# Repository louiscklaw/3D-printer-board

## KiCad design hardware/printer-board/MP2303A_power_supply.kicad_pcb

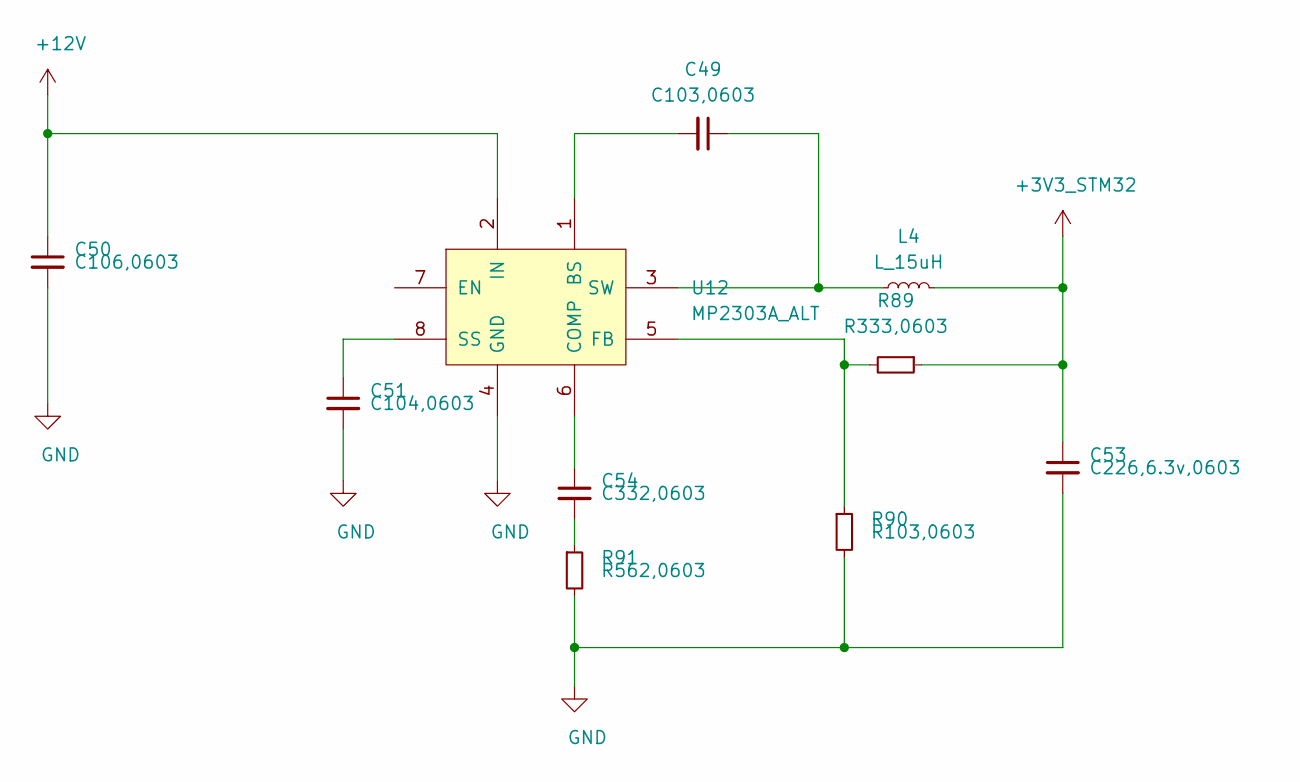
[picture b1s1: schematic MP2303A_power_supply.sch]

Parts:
C49: C103,0603; C_0603_1608Metric_Pad1.05x0.95mm_HandSolder
C50: C106,0603; C_0603_1608Metric_Pad1.05x0.95mm_HandSolder
C51: C104,0603; C_0603_1608Metric_Pad1.05x0.95mm_HandSolder
C53: C226,6.3v,0603; C_0603_1608Metric_Pad1.05x0.95mm_HandSolder
C54: C332,0603; C_0603_1608Metric_Pad1.05x0.95mm_HandSolder
L4: L_15uH; inductor_smd_4.8x2.8mm
R89: R333,0603; R_0603_1608Metric_Pad1.05x0.95mm_HandSolder
R90: R103,0603; R_0603_1608Metric_Pad1.05x0.95mm_HandSolder
R91: R562,0603; R_0603_1608Metric_Pad1.05x0.95mm_HandSolder
U12: MP2303A_ALT; SOIC-8_3.9x4.9mm_P1.27mm

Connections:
+3V3_STM32: C53.1, L4.2, R89.1
+12V: C50.1, U12.2 (IN)
GND: C50.2, C51.2, C53.2, R90.2, R91.2, U12.4 (GND)
unnamed: C49.1, L4.1, U12.3 (SW)
unnamed: C49.2, U12.1 (BS)
unnamed: C51.1, U12.8 (SS)
unnamed: C54.1, U12.6 (COMP)
unnamed: C54.2, R91.1
unnamed: R89.2, R90.1, U12.5 (FB)

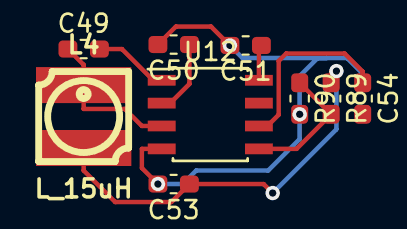
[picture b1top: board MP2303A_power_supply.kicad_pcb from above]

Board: 2 copper layers, 10 parts (1 on the bottom side), 9 nets.

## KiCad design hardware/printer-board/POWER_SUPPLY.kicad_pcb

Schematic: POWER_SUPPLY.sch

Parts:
C19: C104,0603; C_0603_1608Metric_Pad1.05x0.95mm_HandSolder
C20: CP100uf,35V; CP_Elec_6.3x7.7
D15, D16: SD_M4; D_SOD-323_HandSoldering
F1: 16V/30A; fuse_smf
F2: 30V/5A; fuse_smf
J25: 12V_INPUT_2; mpt_0,5%2f2-2,54,12V_SRC
J26: 12V_INPUT; mpt_0,5%2f2-2,54,12V_SRC
J27: 12V_OUT; mpt_0,5%2f2-2,54,12V_SRC
JP5: Jumper_NO_Small; SolderJumper-2_P1.3mm_Open_TrianglePad1.0x1.5mm

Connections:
+12V: C19.1, C20.1, D15.1, D16.2, F2.2, J27.1
+12V2: F1.2
/AM-VIN: D16.1
GND: C19.2, C20.2, D15.2, J25.2, J26.2, J27.2
unnamed: F1.1, J25.1, JP5.1
unnamed: F2.1, J26.1, JP5.2

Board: 2 copper layers, 10 parts (1 on the bottom side), 4 nets, no tracks yet.

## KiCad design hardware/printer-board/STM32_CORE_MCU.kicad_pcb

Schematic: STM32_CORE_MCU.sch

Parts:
C21, C23, C25, C26, C27, C28, C30, C31, C32: C104,0603; C_0603_1608Metric_Pad1.05x0.95mm_HandSolder
C22, C24: C10pf,0603; C_0603_1608Metric_Pad1.05x0.95mm_HandSolder
C29, C55: C105,0603; C_0603_1608Metric_Pad1.05x0.95mm_HandSolder
D17: PB9; LED_0603_1608Metric_Pad1.05x0.95mm_HandSolder
J28: SWD; PinHeader_1x04_P1.27mm_Vertical
JP6, JP7: Jumper_NO_Small; SolderJumper-2_P1.3mm_Open_TrianglePad1.0x1.5mm
L1: L_Small; inductor_smd_0603
R40, R41: R472,0603; R_0603_1608Metric_Pad1.05x0.95mm_HandSolder
R42, R43: R0,0603; R_0603_1608Metric_Pad1.05x0.95mm_HandSolder
R44: R102,0603; R_0603_1608Metric_Pad1.05x0.95mm_HandSolder
R45, R46: R103,0603; R_0603_1608Metric_Pad1.05x0.95mm_HandSolder
SW1: SW_Push; SW_SPST_CK_RS282G05A3
U8: STM32F407VET6; TQFP-100
Y1: O_8M; Crystal_HC49-4H_Vertical

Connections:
+3V3_STM32: C25.2, C26.2, C27.2, C28.2, C29.2, C55.2, D17.2, J28.4, L1.1, R40.2, R41.2, R42.2, U8.11 (VDD_5), U8.22 (VDDA), U8.28 (VDD_4), U8.50 (VDD_1), U8.75 (VDD_2), U8.100 (VDD_3)
/BOOT0: JP6.2, R46.1, U8.94 (BOOT0)
/BOOT1: JP7.2, R45.1, U8.37 (PB2/BOOT1)
/D+: U8.71 (PA12/D+)
/D-: U8.70 (PA11/D-)
/GND-CAP1: C30.1, U8.49 (VSS_1/VCAP_1)
/GND-CAP2: C31.1, U8.73 (NC/VCAP_2)
/GND-VCC3V3: R42.1, R43.1, U8.19 (VSSA/VDD)
/RESET: C32.1, SW1.2, U8.14 (NRST)
/SCL1: U8.92 (PB6/SCL1)
/SDA1: U8.93 (PB7/SDA1)
/SWCLK: J28.2, U8.76 (PA14/JTCK/SWCLK)
/SWDIO: J28.3, U8.72 (PA13/JTMS/SWDIO)
GND: C21.2, C22.2, C23.2, C24.2, C25.1, C26.1, C27.1, C28.1, C29.1, C30.2, C31.2, C32.2, C55.1, J28.1, R43.2, R45.2, R46.2, SW1.1, U8.10 (VSS_5), U8.20 (VREF-), U8.27 (VSS_4), U8.74 (VSS_2), U8.99 (VSS_3)
unnamed: C21.1, L1.2, U8.21 (VREF+)
unnamed: C22.1, U8.12 (OSC_IN), Y1.1
unnamed: C23.1, U8.6 (VBAT)
unnamed: C24.1, U8.13 (OSC_OUT), Y1.2
unnamed: D17.1, R44.2
unnamed: JP6.1, R40.1
unnamed: JP7.1, R41.1
PA0: U8.23 (PA0/WKUP/ADC0)
PA1: U8.24 (PA1/ADC1)
PA2: U8.25 (PA2/ADC2/TX2)
PA3: U8.26 (PA3/ADC3/RX2)
PA4: U8.29 (PA4/ADC4/NSS1)
PA5: U8.30 (PA5/ADC5/SCK1)
PA6: U8.31 (PA6/ADC6/MISO1)
PA7: U8.32 (PA7/ADC7/MOSI1)
PA8: U8.67 (PA8/MCO)
PA9: U8.68 (PA9/TX1)
PA10: U8.69 (PA10/RX1)
PA15: U8.77 (PA15/JTDI)
PB0: U8.35 (PB0/ADC8)
PB1: U8.36 (PB1/ADC9)
PB3: U8.89 (PB3/JTD0)
PB4: U8.90 (PB4/JNTRST)
PB5: U8.91 (PB5)
PB8: U8.95 (PB8)
PB9: R44.1, U8.96 (PB9)
PB10: U8.47 (PB10/SCL2/TX3)
PB11: U8.48 (PB11/SDA2/RX3)
PB12: U8.51 (PB12/NSS2)
PB13: U8.52 (PB13/SCK2)
PB14: U8.53 (PB14/MISO2)
PB15: U8.54 (PBI5/MOSI2)
PC0: U8.15 (PCO/ADC10)
PC1: U8.16 (PC1/ADC11)
PC2: U8.17 (PC2/ADC12)
PC3: U8.18 (PC3/ADC13)
PC4: U8.33 (PC4/ADC14)
PC5: U8.34 (PC5/ADC15)
PC6: U8.63 (PC6)
PC7: U8.64 (PC7)
PC8: U8.65 (PC8)
PC9: U8.66 (PC9)
PC10: U8.78 (PC10)
PC11: U8.79 (PC11)
PC12: U8.80 (PC12)
PC13: U8.7 (PC13/TAMP/RTC)
PC14: U8.8 (PC14/OSCIN)
PC15: U8.9 (PC15/OSCOUT)
PD0: U8.81 (PD0)
PD1: U8.82 (PD1)
PD2: U8.83 (PD2)
PD3: U8.84 (PD3)
PD4: U8.85 (PD4)
PD5: U8.86 (PD5)
PD6: U8.87 (PD6)
PD7: U8.88 (PD7)
PD8: U8.55 (PD8)
PD9: U8.56 (PD9)
PD10: U8.57 (PD10)
PD11: U8.58 (PD11)
PD12: U8.59 (PD12)
PD13: U8.60 (PD13)
PD14: U8.61 (Pd14)
PD15: U8.62 (PD15)
PE0: U8.97 (PE0)
PE1: U8.98 (PE1)
PE2: U8.1 (PE2)
PE3: U8.2 (PE3)
PE4: U8.3 (PE4)
PE5: U8.4 (PE5)
PE6: U8.5 (PE6)
PE7: U8.38 (PE7)
PE8: U8.39 (PE8)
PE9: U8.40 (PE9)
PE10: U8.41 (PE10)
PE11: U8.42 (PE11)
PE12: U8.43 (PE12)
PE13: U8.44 (PE13)
PE14: U8.45 (PE14)
PE15: U8.46 (PE15)

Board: 2 copper layers, 28 parts (22 on the bottom side), 18 nets, no tracks yet.

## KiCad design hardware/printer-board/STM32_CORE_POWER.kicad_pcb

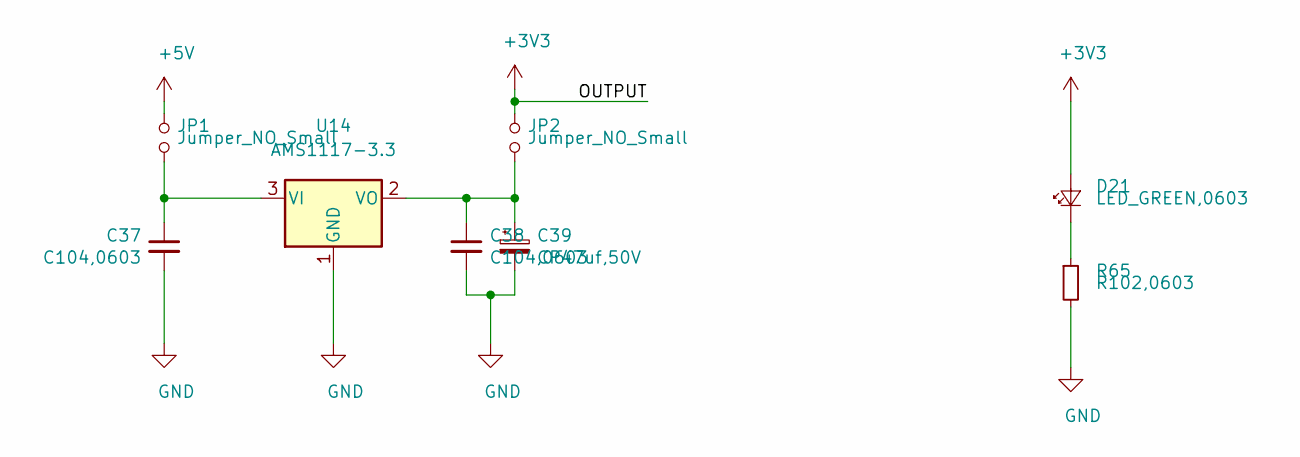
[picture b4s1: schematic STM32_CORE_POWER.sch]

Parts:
C37, C38: C104,0603; C_0603_1608Metric_Pad1.05x0.95mm_HandSolder
C39: CP47uf,50V; c_elec_6.3x7.7
D21: LED_GREEN,0603; LED_0603_1608Metric_Pad1.05x0.95mm_HandSolder
JP1, JP2: Jumper_NO_Small; SolderJumper-2_P1.3mm_Bridged2Bar_RoundedPad1.0x1.5mm
R65: R102,0603; R_0603_1608Metric_Pad1.05x0.95mm_HandSolder
U14: AMS1117-3.3; SOT-223-3_TabPin2

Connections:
+3V3: D21.2 (A), JP2.1
+5V: JP1.1
GND: C37.2, C38.2, C39.2, R65.2, U14.1 (GND)
unnamed: C37.1, JP1.2, U14.3 (VI)
unnamed: C38.1, C39.1, JP2.2, U14.2 (VO)
unnamed: D21.1 (K), R65.1

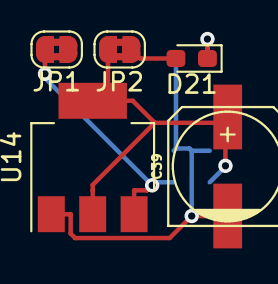
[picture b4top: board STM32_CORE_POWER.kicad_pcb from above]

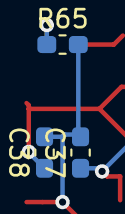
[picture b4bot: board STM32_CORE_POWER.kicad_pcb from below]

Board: 2 copper layers, 8 parts (3 on the bottom side), 5 nets.

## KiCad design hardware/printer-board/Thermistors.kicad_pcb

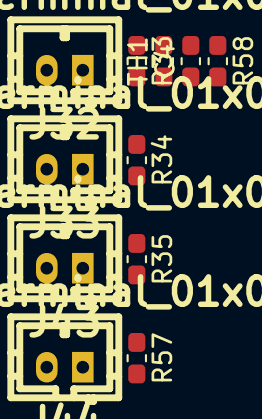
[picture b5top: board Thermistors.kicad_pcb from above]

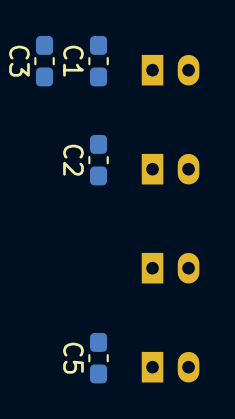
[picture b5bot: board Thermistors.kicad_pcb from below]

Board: 2 copper layers, 15 parts (4 on the bottom side), 7 nets, no tracks yet.

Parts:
C1, C2, C3, C4, C5: C105,0603; C_0603_1608Metric_Pad1.05x0.95mm_HandSolder
J32, J33, J43, J44: Screw_Terminal_01x02; b2b-ph-kl
R33, R34, R35, R57, R58: R472,0603; R_0603_1608Metric_Pad1.05x0.95mm_HandSolder
TH1: Thermistor_NTC; R_0603_1608Metric_Pad1.05x0.95mm_HandSolder

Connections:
+3V3_STM32: R33.1, R34.1, R35.1, R57.1, R58.1
/AUX_TEMP: C2.1, J33.1, R34.2
/HEATBED_TEMP: C1.1, J32.1, R33.2
/HOTEND_TEMP1: C3.1, J43.1, R35.2
/HOTEND_TEMP2: C5.1, J44.1, R57.2
/PCB_TEMP: C4.1, R58.2, TH1.1
GND: C1.2, C2.2, C3.2, C4.2, C5.2, J32.2, J33.2, J43.2, J44.2, TH1.2

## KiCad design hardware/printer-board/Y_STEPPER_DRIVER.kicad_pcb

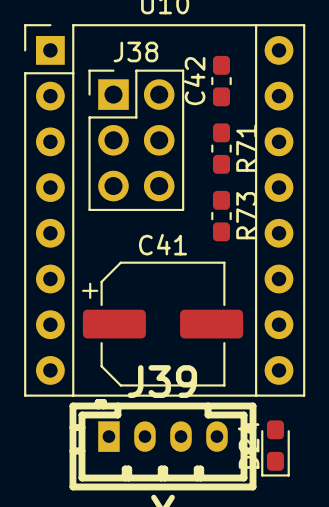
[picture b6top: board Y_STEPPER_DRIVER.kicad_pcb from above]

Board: 2 copper layers, 9 parts (1 on the bottom side), 13 nets, no tracks yet.

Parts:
C41: CP100uf,25V; CP_Elec_6.3x7.7
C42: C104,0603; C_0603_1608Metric_Pad1.05x0.95mm_HandSolder
D24: LED_BLUE,0603; LED_0603_1608Metric_Pad1.05x0.95mm_HandSolder
J38: MS_SELECT; PinHeader_2x03_P2.54mm_Vertical
J39: Y; b4b-ph-kl,stepper_terminal
R71: R104,0603; R_0603_1608Metric_Pad1.05x0.95mm_HandSolder
R72: R102,0603; R_0603_1608Metric_Pad1.05x0.95mm_HandSolder
R73: R103,0603; R_0603_1608Metric_Pad1.05x0.95mm_HandSolder
U10: A4988_MODULE; Pololu_Breakout-16_15.2x20.3mm

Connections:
+3V3_STM32: C42.2, J38.2, J38.4, J38.6, R72.1, R73.1, U10.10
+12V: C41.1, U10.16
/~Y_EN~: D24.1, R73.2, U10.1
GND: C41.2, C42.1, R71.1, U10.9, U10.15
unnamed: D24.2, R72.2
unnamed: J38.1, R71.2, U10.2
unnamed: J38.3, U10.3
unnamed: J38.5, U10.4
unnamed: J39.1, U10.14
unnamed: J39.2, U10.13
unnamed: J39.3, U10.12
unnamed: J39.4, U10.11
unnamed: U10.5, U10.6

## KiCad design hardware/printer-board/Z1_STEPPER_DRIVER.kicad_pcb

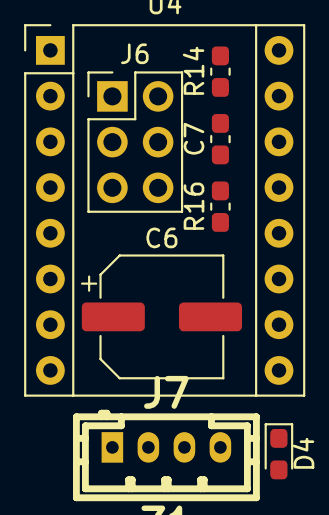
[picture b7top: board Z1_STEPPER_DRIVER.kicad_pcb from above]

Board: 2 copper layers, 9 parts (1 on the bottom side), 13 nets, no tracks yet.

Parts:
C6: CP100uf,25V; CP_Elec_6.3x7.7
C7: C104,0603; C_0603_1608Metric_Pad1.05x0.95mm_HandSolder
D4: LED_BLUE,0603; LED_0603_1608Metric_Pad1.05x0.95mm_HandSolder
J6: MS_SELECT; PinHeader_2x03_P2.54mm_Vertical
J7: Z1; b4b-ph-kl,stepper_terminal
R14: R104,0603; R_0603_1608Metric_Pad1.05x0.95mm_HandSolder
R15: R102,0603; R_0603_1608Metric_Pad1.05x0.95mm_HandSolder
R16: R103,0603; R_0603_1608Metric_Pad1.05x0.95mm_HandSolder
U4: A4988_MODULE; Pololu_Breakout-16_15.2x20.3mm

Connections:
+3V3_STM32: C7.2, J6.2, J6.4, J6.6, R15.1, R16.1, U4.10
+12V: C6.1, U4.16
/~Z1_EN~: D4.1, R16.2, U4.1
GND: C6.2, C7.1, R14.1, U4.9, U4.15
unnamed: D4.2, R15.2
unnamed: J6.1, R14.2, U4.2
unnamed: J6.3, U4.3
unnamed: J6.5, U4.4
unnamed: J7.1, U4.14
unnamed: J7.2, U4.13
unnamed: J7.3, U4.12
unnamed: J7.4, U4.11
unnamed: U4.5, U4.6
